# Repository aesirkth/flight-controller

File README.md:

# Flight Controller <!-- omit in toc -->

This is the embedded software on the Flight Controller for the project Mjollnir. The Flight Controller is on-board the rocket. The Flight Controller communicates with the ground through a radio link during all phases of the flight

The mission objectives for the Mjollnir project relevant to the electronics are the following:

**Primary objectives**

- **E.PO.1** Monitor the rocket while it is on the launchpad and give a “Go”/”No go” signal
- **E.PO.2** Control the rocket while it is on the launchpad
- **E.PO.3** Trigger the drogue parachute’s ejection after apogee
- **E.PO.4** Trigger the main parachute’s ejection before touchdown
- **E.PO.5** Support rocket recovery operations
- **E.PO.6** Record video footage from the rocket

**Secondary objectives**

- **E.SO.1** Send real-time telemetry from the rocket
- **E.SO.2** Receive & display real-time telemetry from the rocket at the Ground Station as long as the rocket is at a reasonable distance
- **E.SO.3** Send real-time video from the rocket
- **E.SO.4** Receive & display real-time video from the rocket at the Ground Station as long as the rocket is at a reasonable distance
- **E.SO.5** Acquire flight data with more sensors than those deemed “mission-critical”
- **E.SO.6** Store all flight data on-board the rocket for further analysis

All of them apply to some extent to the Flight Controller

# Table of content <!-- omit in toc -->

- [Description](#description)
  - [Hardware](#hardware)
  - [Software](#software)
    - [Installation](#installation)
  - [Tests](#tests)
- [Data protocol](#data-protocol)
- [Folder structure](#folder-structure)

# Description

## Hardware

The Flight Controller is a single PCB with power management, sensors, radio communication, and driver for the actuators used during the flight.

It has the following features:

- Dual microcontroller (main + backup)
- Low power long range LoRa transceiver
- Telemetry output via serial link (x3)
- GNSS support via serial link (x3)
- Compatible with 10 dof breakout board with MS5611 pressure sensors and MPU9250 IMU (2x)
- Compatible with K type thermocouples (2x)
- Flash memory
- EEDs driver for parachute ejection, with ESD protection + visual and audible warning (2x)
- RGB leds to display the board status
- Serial link to FPV transmitter
- CAN Bus

A more detailed description of the hardware is given in [doc/hardware_description.md](doc/hardware_description.md)

## Software

This repository uses [PlatformIO](https://platformio.org/) as the development tool for the two microcontrollers on the Flight Controller.

### Installation

1. Install [PlatformIO Core](https://docs.platformio.org/en/latest/core/index.html) or [PlatformIO IDE](https://platformio.org/install/ide) on your computer
2. Clone this repository
3. [Linux] install [udev](https://docs.platformio.org/en/latest/faq.html?highlight=99#platformio-udev-rules) rules

## Tests

See [test/](test/)

# Data protocol

The protocol to communicate between the Ground Station and the Rocket is detailed in [doc/data_protocol](doc/data_protocol.md)

# Folder structure

```
.
├── doc/
│   ├── img/
│   ├── diagrams/
│   ├── sources
│   |   └── flight_controller_v1.0.pdf
│   ├── data_protocol.md
│   └── hardware_description.md
├── include/
│   ├── hardware_definition_nano.h
│   └── hardware_definition_teensy.h
├── src/                                    // Code folder
│   └── test_companion_teensy.cpp           // Use with hardware_test_teensy
├── test/                                   // Unit tests
│   ├── hardware_test_nano/
│   ├── hardware_test_teensy/
│   └── README.md                           // Documentation for the tests
├── env_nano.ini                            // Extra platformIO config
├── env_teensy.ini                          // Extra platformIO config
├── LICENSE
├── platformio.ini                          // PlatformIO config
└── README.md                               // This file
```

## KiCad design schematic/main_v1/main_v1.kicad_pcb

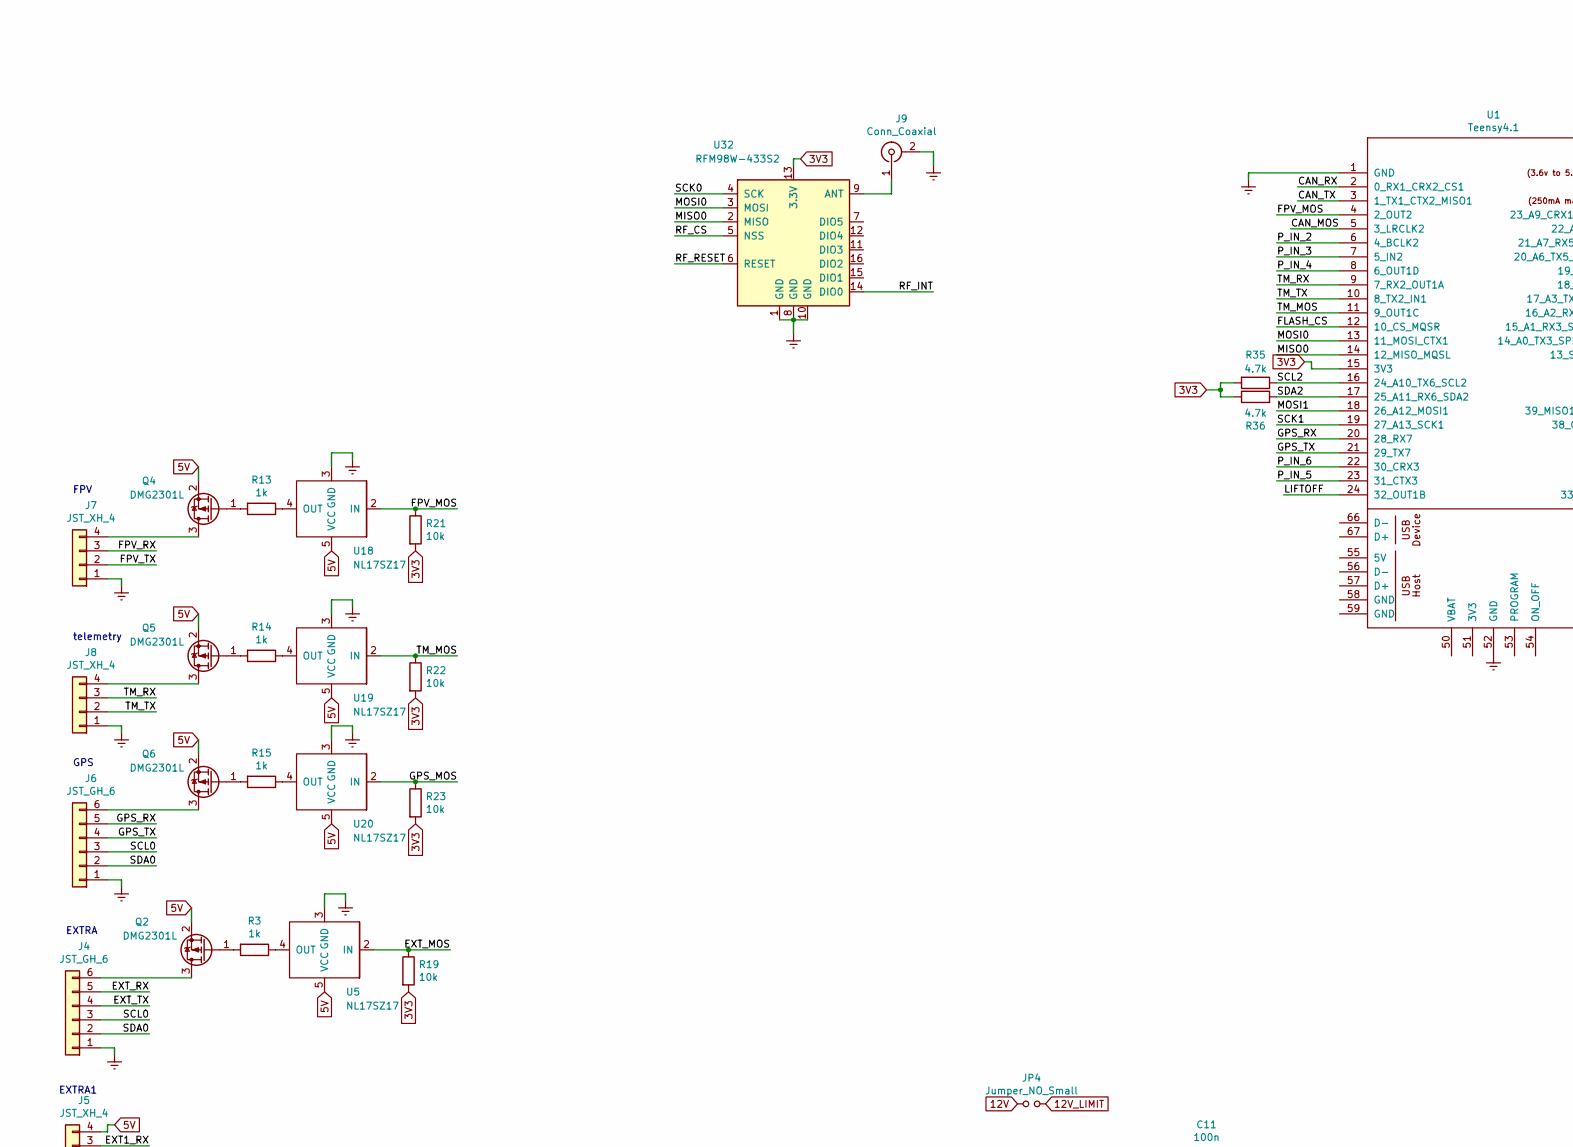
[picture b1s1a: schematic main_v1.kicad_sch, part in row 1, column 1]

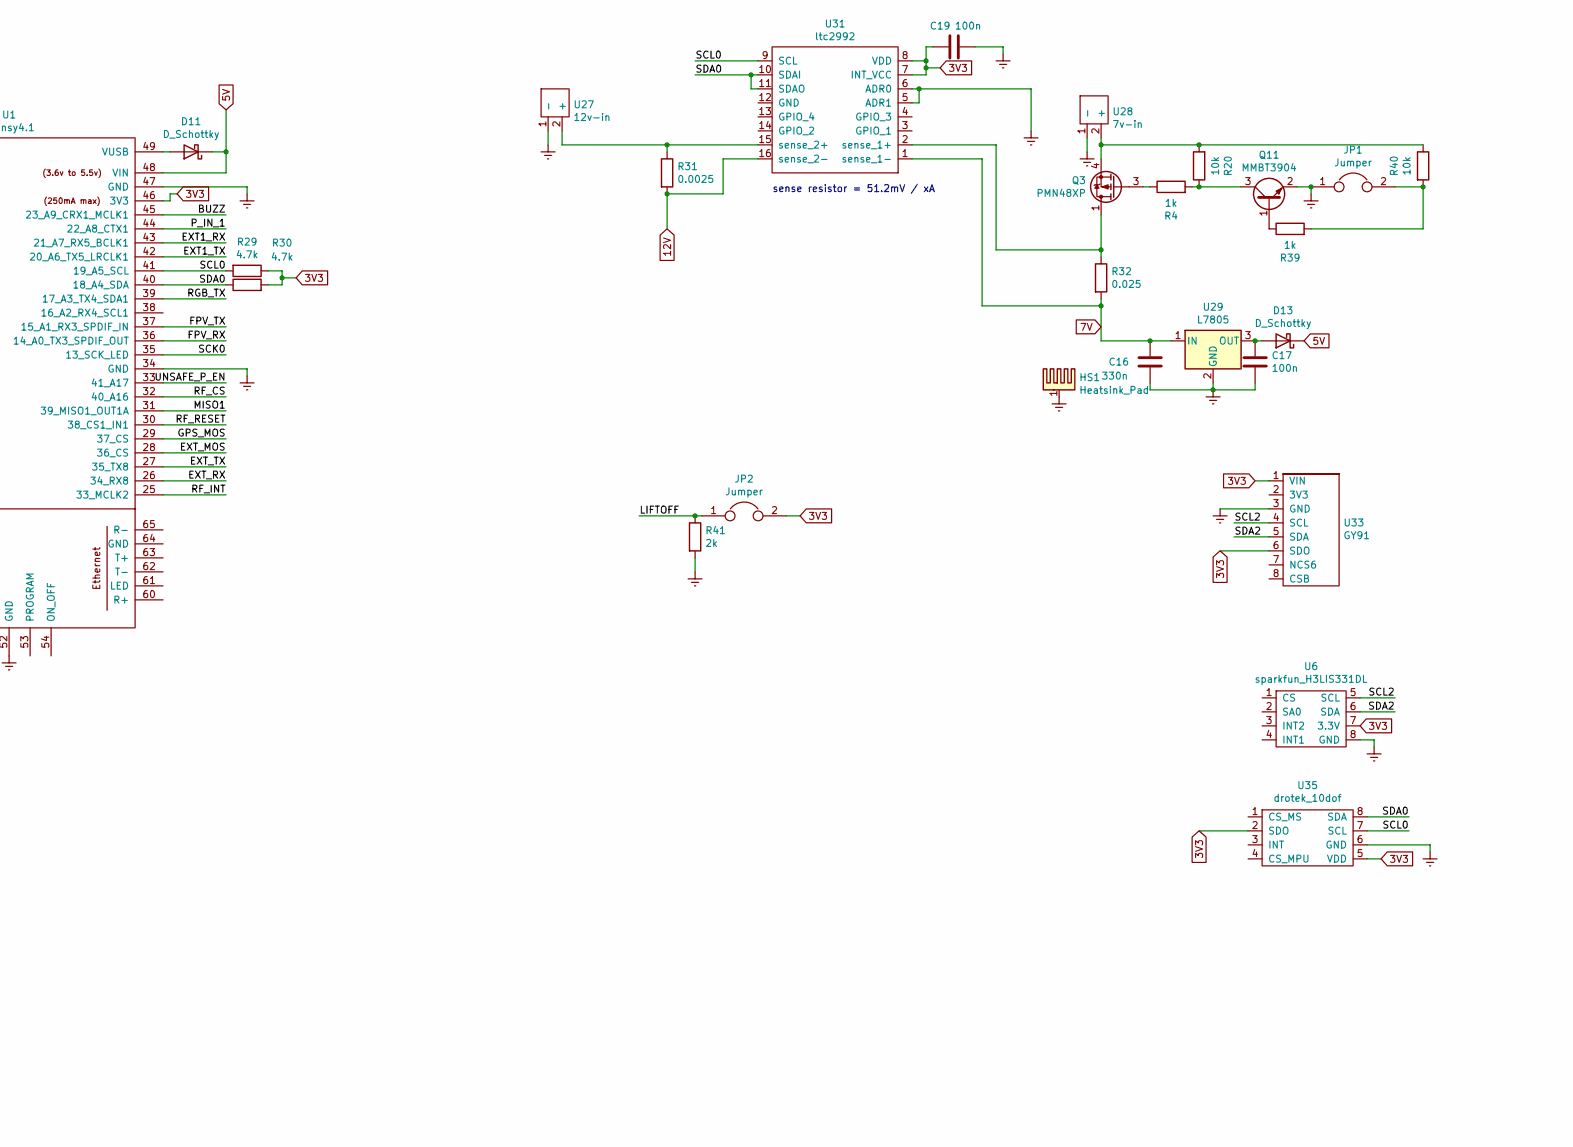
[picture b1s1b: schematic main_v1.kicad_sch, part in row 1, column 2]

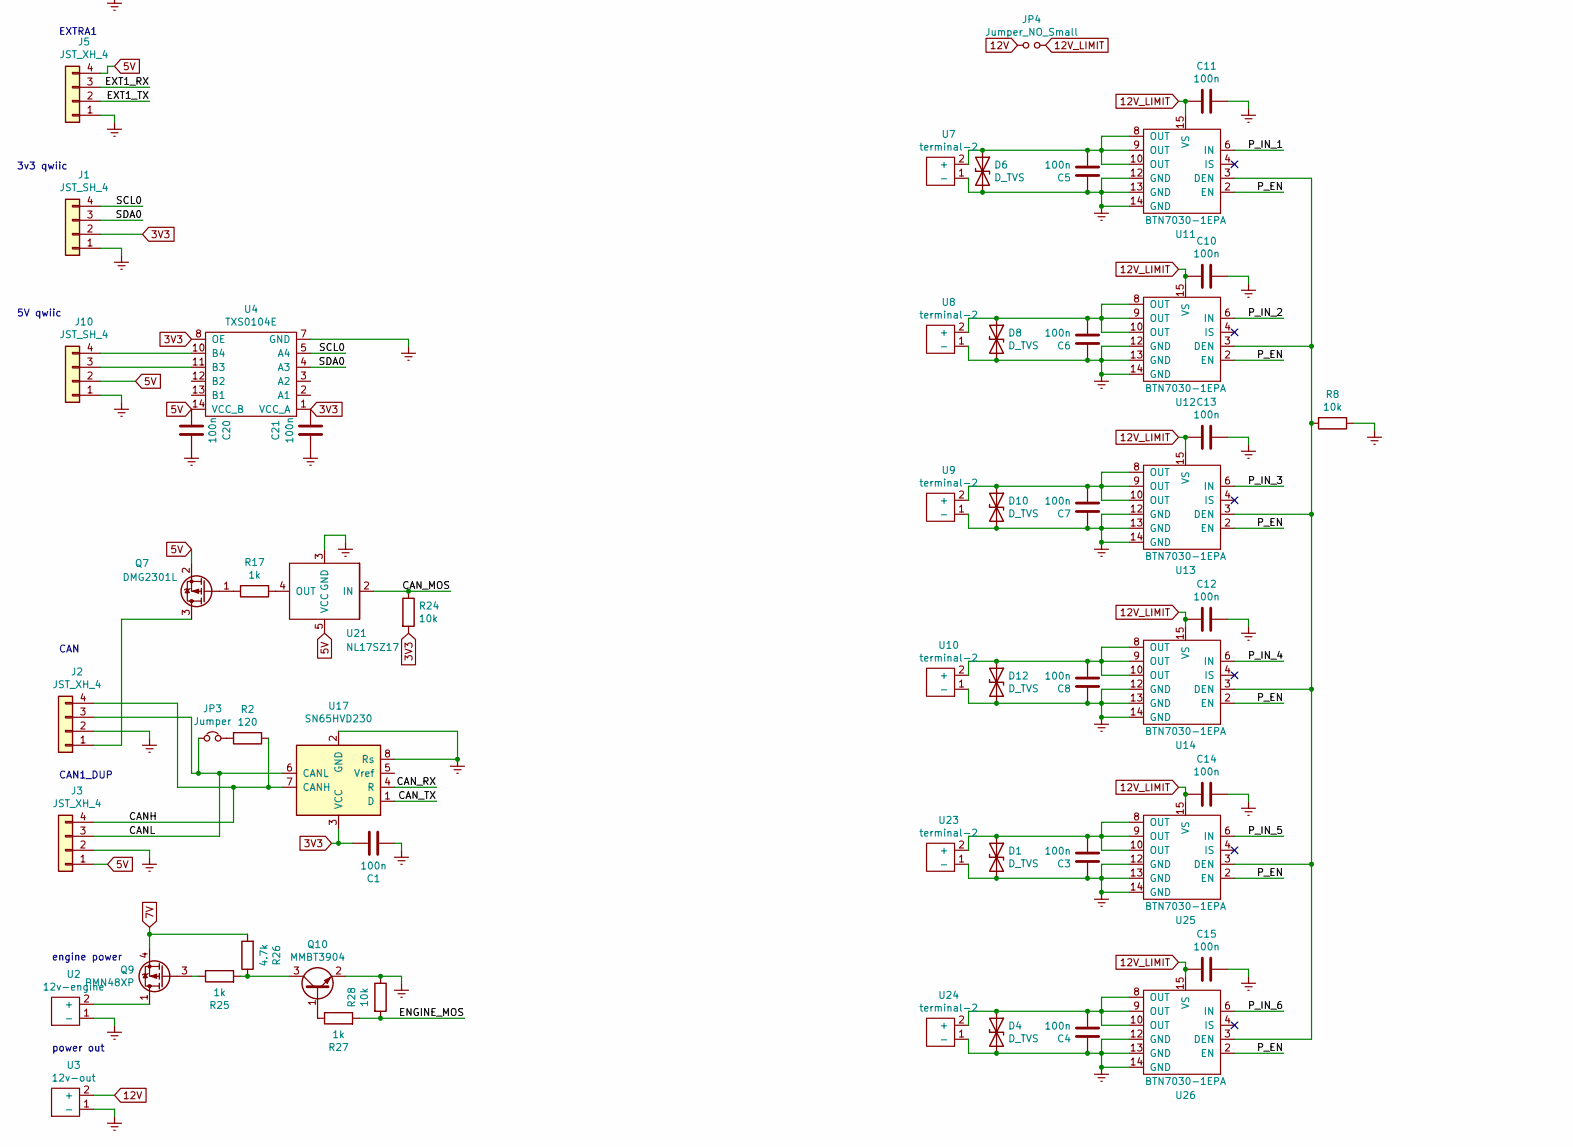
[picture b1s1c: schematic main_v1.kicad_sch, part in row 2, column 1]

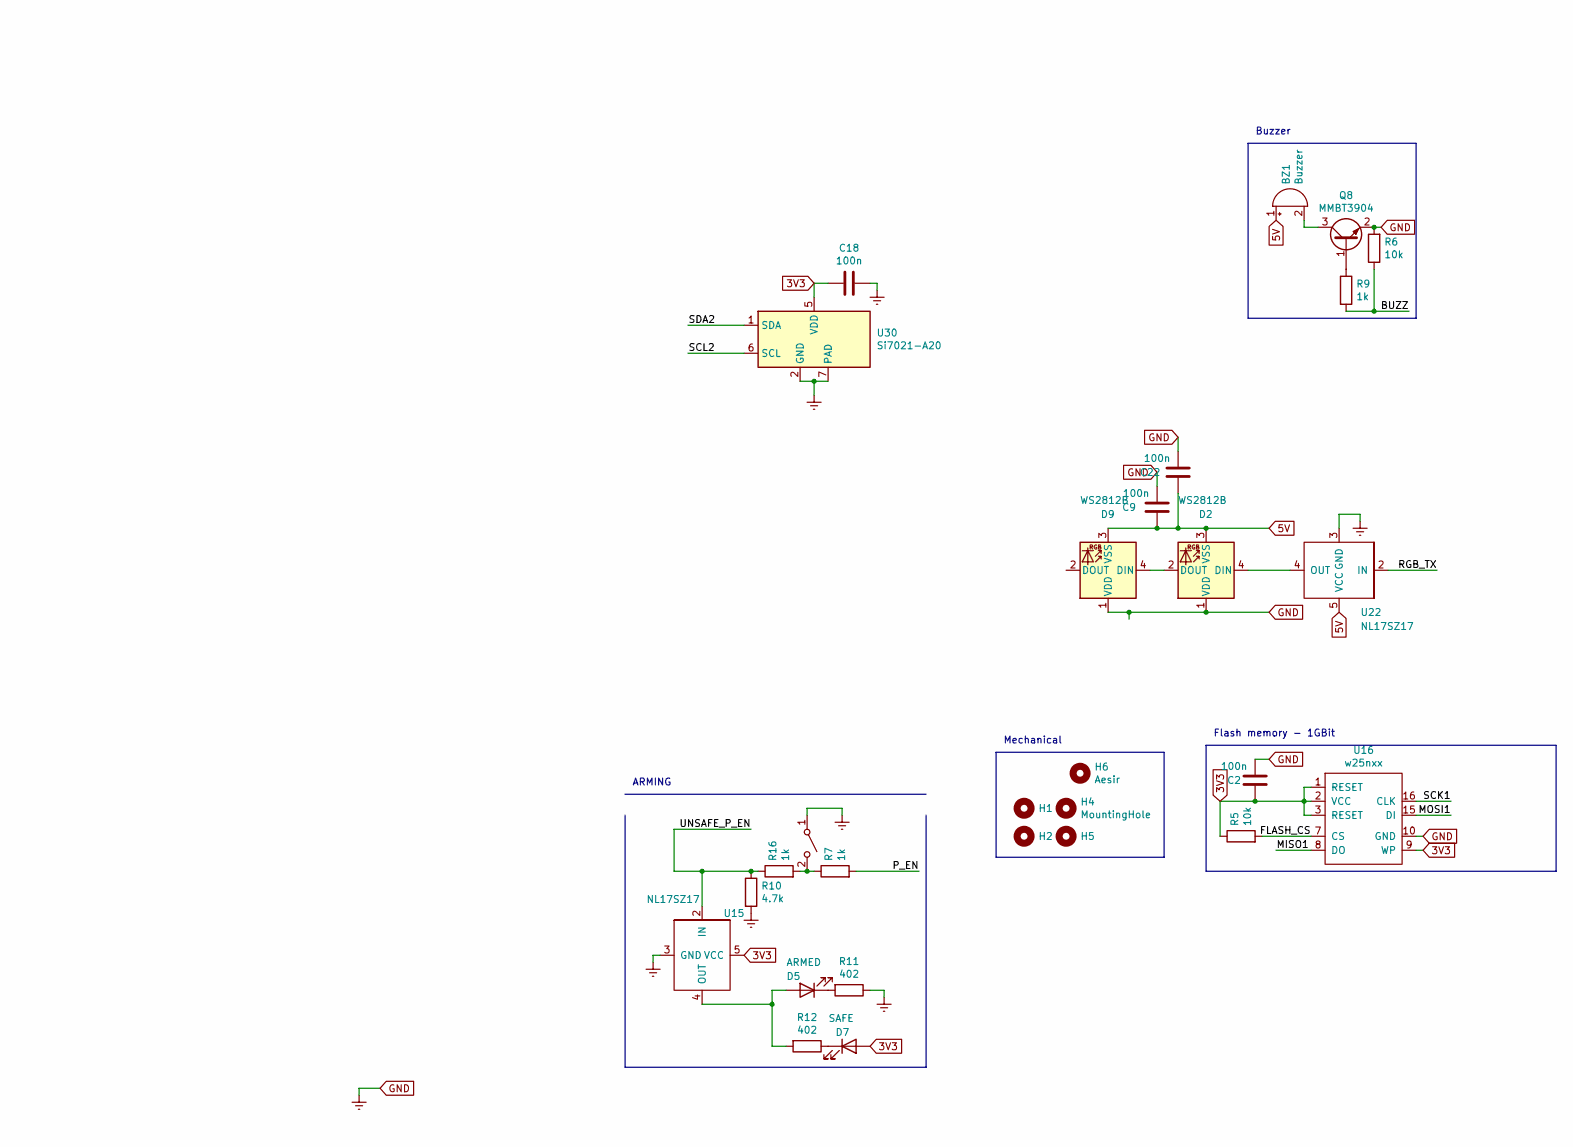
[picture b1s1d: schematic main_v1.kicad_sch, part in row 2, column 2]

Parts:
BZ1: Buzzer; CX-0905C; mouser 490-CX-0905C
C1, C2, C3, C4, C5, C6, C7, C8, C9, C10, C11, C12, C13, C14, C15, C17, C18, C19, C20, C21, C22: 100n; C_0805_2012Metric_Pad1.18x1.45mm_HandSolder; mouser 710-885012207072
C16: 330n; C_0805_2012Metric_Pad1.18x1.45mm_HandSolder; mouser 80-C0805C334K3N
D1, D4, D6, D8, D10, D12: D_TVS; D_0805_2012Metric_Pad1.15x1.40mm_HandSolder; mouser 621-SD15C-7
D2, D9: WS2812B; ws2812-through-hole-5mm
D5: ARMED; LED_0805_2012Metric_Pad1.15x1.40mm_HandSolder; mouser 710-150060AS75000
D7: SAFE; LED_0805_2012Metric_Pad1.15x1.40mm_HandSolder; mouser 710-150060YS75000
D11, D13: D_Schottky; D_SOD-323_HandSoldering; mouser 726-BAT60AE6327XT
H1, H2, H4, H5: MountingHole; MountingHole_3.2mm_M3_ISO14580
H6: Aesir; aesir
HS1: Heatsink_Pad; d2pak_heatsink; mouser 588-DV-T263-201E-TR
J1, J10: JST_SH_4; JST_SH_SM04B-SRSS-TB_1x04-1MP_P1.00mm_Horizontal; mouser 485-4208
J2, J3, J5, J7, J8: JST_XH_4; JST_XH_B4B-XH-A_1x04_P2.50mm_Vertical
J4, J6: JST_GH_6; JST_GH_BM06B-GHS-TBT_1x06-1MP_P1.25mm_Vertical
J9: Conn_Coaxial; SMA_Amphenol_132289_EdgeMount; mouser 712-CONSMA020.062-G
JP1, JP2: Jumper; JST_XH_B2B-XH-A_1x02_P2.50mm_Vertical
JP3: Jumper; PinHeader_1x02_P2.54mm_Vertical
JP4: Jumper_NO_Small; R_1812_4532Metric_Pad1.30x3.40mm_HandSolder_no_silk
Q2, Q4, Q5, Q6, Q7: DMG2301L; SOT-23; mouser 621-DMG2301L-7
Q3, Q9: PMN48XP; TSOP-6_1.65x3.05mm_P0.95mm; mouser 771-PMN48XP,125
Q8, Q10, Q11: MMBT3904; SOT-23; mouser 241-MMBT3904R200001
R2: 120; R_0805_2012Metric_Pad1.20x1.40mm_HandSolder; mouser 652-CR0805FX-1200ELF
R3, R4, R7, R9, R13, R14, R15, R16, R17, R25, R27, R39: 1k; R_0805_2012Metric_Pad1.20x1.40mm_HandSolder; mouser 667-ERJ-6ENF1001V
R5, R6, R8, R19, R20, R21, R22, R23, R24, R28, R40: 10k; R_0805_2012Metric_Pad1.20x1.40mm_HandSolder; mouser 71-CRCW080510K0FKEAC
R10, R26, R29, R30, R35, R36: 4.7k; R_0805_2012Metric_Pad1.20x1.40mm_HandSolder; mouser 652-CR0805FX-4701ELF
R11, R12: 402; R_0805_2012Metric_Pad1.20x1.40mm_HandSolder; mouser 603-RT0805FRE07402RL
R31: 0.0025; R_2512_6332Metric_Pad1.40x3.35mm_HandSolder; mouser 756-ULR1-R0025FT2
R32: 0.025; R_2512_6332Metric_Pad1.40x3.35mm_HandSolder; mouser WSL2512R0250FEB
R41: 2k; R_0805_2012Metric_Pad1.20x1.40mm_HandSolder; mouser 71-CRCW08052K00FKEAC
SW1: SW_DPST_x2; PinHeader_1x02_P2.54mm_Vertical
U1: Teensy4.1; Teensy41
U2: 12v-engine; AMASS_XT30U-F_1x02_P5.0mm_Vertical
U3: 12v-out; AMASS_XT30U-F_1x02_P5.0mm_Vertical
U4: TXS0104E; TSSOP-14_4.4x5mm_P0.65mm; mouser 771-LSF0204PW-Q100J
U5, U15, U18, U19, U20, U21, U22: NL17SZ17; SC-74-a; mouser 863-NL17SZ17DBVT1G
U6: sparkfun_H3LIS331DL; mouser 474-SEN-14480
U7, U8, U9, U10, U23, U24: terminal-2; terminal-small
U11, U12, U13, U14, U25, U26: BTN7030-1EPA; Infineon_PG-TSDSO-14-22-bottom; mouser 726-BTN70301EPAXUMA1
U16: w25nxx; SOIC-16W_7.5x10.3mm_P1.27mm; mouser 454-W25N01GVSFIG
U17: SN65HVD230; SOIC-8_3.9x4.9mm_P1.27mm; mouser 595-SN65HVD231QDRQ1
U27: 12v-in; AMASS_XT60-M_1x02_P7.20mm_Vertical
U28: 7v-in; AMASS_XT30U-M_1x02_P5.0mm_Vertical
U29: L7805; TO-263-2; mouser 511-L7805ABD2T-TR
U30: Si7021-A20; DFN-6-1EP_3x3mm_P1mm_EP1.5x2.4mm; mouser 634-SI7021-A20-IM
U31: ltc2992; MSOP-16_3x4mm_P0.5mm; mouser 584-LTC2992IMSPBF
U32: RFM98W-433S2; HOPERF_RFM9XW_SMD; mouser :(
U33: GY91
U35: drotek_10dof

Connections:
3V3: C1.2, C2.1, C18.2, C19.2, C21.1, D7.2 (A), J1.2, JP2.2, R5.1, R19.2, R21.2, R22.2, R23.2, R24.2, R29.1, R30.2, R35.2, R36.1, U1.15 (3V3), U1.46 (3V3), U4.1 (VCC_A), U4.8 (OE), U6.7 (3.3V), U15.5 (VCC), U16.1 (RESET), U16.2 (VCC), U16.3 (RESET), U16.9 (WP), U17.3 (VCC), U30.5 (VDD), U31.7 (INT_VCC), U31.8 (VDD), U32.13 (3.3V), U33.1 (VIN), U33.6 (SDO), U35.2 (SDO), U35.5 (VDD)
5V: BZ1.1 (-), C9.1, C20.2, C22.1, D2.3 (VSS), D9.3 (VSS), D11.1 (K), D13.1 (K), J3.1, J5.4, J10.2, Q2.2 (S), Q4.2 (S), Q5.2 (S), Q6.2 (S), Q7.2 (S), U1.48 (VIN), U4.14 (VCC_B), U5.5 (VCC), U18.5 (VCC), U19.5 (VCC), U20.5 (VCC), U21.5 (VCC), U22.5 (VCC)
7V: C16.1, Q9.4 (S), R26.2, R32.2, U29.1 (IN), U31.1 (sense_1-)
12V: JP4.1, R31.2, U3.2 (+), U31.16 (sense_2-)
12V_LIMIT: C10.2, C11.2, C12.2, C13.2, C14.2, C15.2, JP4.2, U11.15 (VS), U12.15 (VS), U13.15 (VS), U14.15 (VS), U25.15 (VS), U26.15 (VS)
/BUZZ: R6.1, R9.2, U1.45 (23_A9_CRX1_MCLK1)
/CAN_MOS: R24.1, U1.5 (3_LRCLK2), U21.2 (IN)
/CAN_RX: U1.2 (0_RX1_CRX2_CS1), U17.4 (R)
/CAN_TX: U1.3 (1_TX1_CTX2_MISO1), U17.1 (D)
/ENGINE_MOS: R27.2, R28.2
/EXT1_RX: J5.3, U1.43 (21_A7_RX5_BCLK1)
/EXT1_TX: J5.2, U1.42 (20_A6_TX5_LRCLK1)
/EXT_MOS: R19.1, U1.28 (36_CS), U5.2 (IN)
/EXT_RX: J4.5, U1.26 (34_RX8)
/EXT_TX: J4.4, U1.27 (35_TX8)
/FLASH_CS: R5.2, U1.12 (10_CS_MQSR), U16.7 (CS)
/FPV_MOS: R21.1, U1.4 (2_OUT2), U18.2 (IN)
/FPV_RX: J7.3, U1.36 (14_A0_TX3_SPDIF_OUT)
/FPV_TX: J7.2, U1.37 (15_A1_RX3_SPDIF_IN)
/GPS_MOS: R23.1, U1.29 (37_CS), U20.2 (IN)
/GPS_RX: J6.5, U1.20 (28_RX7)
/GPS_TX: J6.4, U1.21 (29_TX7)
/LIFTOFF: JP2.1, R41.1, U1.24 (32_OUT1B)
/MISO0: U1.14 (12_MISO_MQSL), U32.2 (MISO)
/MISO1: U1.31 (39_MISO1_OUT1A), U16.8 (DO)
/MOSI0: U1.13 (11_MOSI_CTX1), U32.3 (MOSI)
/MOSI1: U1.18 (26_A12_MOSI1), U16.15 (DI)
/P_EN: R7.2, U11.2 (EN), U12.2 (EN), U13.2 (EN), U14.2 (EN), U25.2 (EN), U26.2 (EN)
/P_IN_1: U1.44 (22_A8_CTX1), U11.6 (IN)
/P_IN_2: U1.6 (4_BCLK2), U12.6 (IN)
/P_IN_3: U1.7 (5_IN2), U13.6 (IN)
/P_IN_4: U1.8 (6_OUT1D), U14.6 (IN)
/P_IN_5: U1.23 (31_CTX3), U25.6 (IN)
/P_IN_6: U1.22 (30_CRX3), U26.6 (IN)
/RF_CS: U1.32 (40_A16), U32.5 (NSS)
/RF_INT: U1.25 (33_MCLK2), U32.14 (DIO0)
/RF_RESET: U1.30 (38_CS1_IN1), U32.6 (RESET)
/RGB_TX: U1.39 (17_A3_TX4_SDA1), U22.2 (IN)
/SCK0: U1.35 (13_SCK_LED), U32.4 (SCK)
/SCK1: U1.19 (27_A13_SCK1), U16.16 (CLK)
/SCL0: J1.4, J4.3, J6.3, R29.2, U1.41 (19_A5_SCL), U4.5 (A4), U31.9 (SCL), U35.7 (SCL)
/SCL2: R35.1, U1.16 (24_A10_TX6_SCL2), U6.5 (SCL), U30.6 (SCL), U33.4 (SCL)
/SDA0: J1.3, J4.2, J6.2, R30.1, U1.40 (18_A4_SDA), U4.4 (A3), U31.10 (SDAI), U31.11 (SDAO), U35.8 (SDA)
/SDA2: R36.2, U1.17 (25_A11_RX6_SDA2), U6.6 (SDA), U30.1 (SDA), U33.5 (SDA)
/TM_MOS: R22.1, U1.11 (9_OUT1C), U19.2 (IN)
/TM_RX: J8.3, U1.9 (7_RX2_OUT1A)
/TM_TX: J8.2, U1.10 (8_TX2_IN1)
/UNSAFE_P_EN: R10.1, R16.1, U1.33 (41_A17), U15.2 (IN)
GND: C1.1, C2.2, C3.1, C4.1, C5.1, C6.1, C7.1, C8.1, C9.2, C10.1, C11.1, C12.1, C13.1, C14.1, C15.1, C16.2, C17.2, C18.1, C19.1, C20.1, C21.2, C22.2, D1.2 (A2), D2.1 (VDD), D4.2 (A2), D6.2 (A2), D8.2 (A2), D9.1 (VDD), D10.2 (A2), D12.2 (A2), HS1.1, J1.1, J2.2, J3.2, J4.1, J5.1, J6.1, J7.1, J8.1, J9.2 (Ext), J10.1, JP1.1, Q8.2 (E), Q10.2 (E), Q11.2 (E), R6.2, R8.1, R10.2, R11.1, R28.1, R41.2, SW1.1 (A), U1.1 (GND), U1.34 (GND), U1.47 (GND), U1.52 (GND), U2.1 (-), U3.1 (-), U4.7 (GND), U5.3 (GND), U6.8 (GND), U7.1 (-), U8.1 (-), U9.1 (-), U10.1 (-), U11.12 (GND), U11.13 (GND), U11.14 (GND), U12.12 (GND), U12.13 (GND), U12.14 (GND), U13.12 (GND), U13.13 (GND), U13.14 (GND), U14.12 (GND), U14.13 (GND), U14.14 (GND), U15.3 (GND), U16.10 (GND), U17.2 (GND), U17.8 (Rs), U18.3 (GND), U19.3 (GND), U20.3 (GND), U21.3 (GND), U22.3 (GND), U23.1 (-), U24.1 (-), U25.12 (GND), U25.13 (GND), U25.14 (GND), U26.12 (GND), U26.13 (GND), U26.14 (GND), U27.1 (-), U28.1 (-), U29.2 (GND), U30.2 (GND), U30.7 (PAD), U31.5 (ADR1), U31.6 (ADR0), U32.1 (GND), U32.8 (GND), U32.10 (GND), U33.3 (GND), U35.6 (GND)
unnamed: BZ1.2 (+), Q8.3 (C)
unnamed: C3.2, D1.1 (A1), U23.2 (+), U25.8 (OUT), U25.9 (OUT), U25.10 (OUT)
unnamed: C4.2, D4.1 (A1), U24.2 (+), U26.8 (OUT), U26.9 (OUT), U26.10 (OUT)
unnamed: C5.2, D6.1 (A1), U7.2 (+), U11.8 (OUT), U11.9 (OUT), U11.10 (OUT)
unnamed: C6.2, D8.1 (A1), U8.2 (+), U12.8 (OUT), U12.9 (OUT), U12.10 (OUT)
unnamed: C7.2, D10.1 (A1), U9.2 (+), U13.8 (OUT), U13.9 (OUT), U13.10 (OUT)
unnamed: C8.2, D12.1 (A1), U10.2 (+), U14.8 (OUT), U14.9 (OUT), U14.10 (OUT)
unnamed: C17.1, D13.2 (A), U29.3 (OUT)
unnamed: D2.2 (DOUT), D9.4 (DIN)
unnamed: D2.4 (DIN), U22.4 (OUT)
unnamed: D5.1 (K), R11.2
unnamed: D5.2 (A), R12.2, U15.4 (OUT)
unnamed: D7.1 (K), R12.1
unnamed: D11.2 (A), U1.49 (VUSB)
unnamed: J2.1, Q7.3 (D)
unnamed: J2.3, J3.3, JP3.1, U17.6 (CANL)
unnamed: J2.4, J3.4, R2.1, U17.7 (CANH)
unnamed: J4.6, Q2.3 (D)
unnamed: J6.6, Q6.3 (D)
unnamed: J7.4, Q4.3 (D)
unnamed: J8.4, Q5.3 (D)
unnamed: J9.1 (In), U32.9 (ANT)
unnamed: J10.3, U4.11 (B3)
unnamed: J10.4, U4.10 (B4)
unnamed: JP1.2, R39.2, R40.2
unnamed: JP3.2, R2.2
unnamed: Q2.1 (G), R3.2
unnamed: Q3.1 (D), Q3.2 (D), Q3.5 (D), Q3.6 (D), R32.1, U31.2 (sense_1+)
unnamed: Q3.3 (G), R4.1
unnamed: Q3.4 (S), R20.2, R40.1, U28.2 (+)
unnamed: Q4.1 (G), R13.2
unnamed: Q5.1 (G), R14.2
unnamed: Q6.1 (G), R15.2
unnamed: Q7.1 (G), R17.2
unnamed: Q8.1 (B), R9.1
unnamed: Q9.1 (D), Q9.2 (D), Q9.5 (D), Q9.6 (D), U2.2 (+)
unnamed: Q9.3 (G), R25.1
unnamed: Q10.1 (B), R27.1
unnamed: Q10.3 (C), R25.2, R26.1
unnamed: Q11.1 (B), R39.1
unnamed: Q11.3 (C), R4.2, R20.1
unnamed: R3.1, U5.4 (OUT)
unnamed: R8.2, U11.3 (DEN), U12.3 (DEN), U13.3 (DEN), U14.3 (DEN), U25.3 (DEN), U26.3 (DEN)
unnamed: R13.1, U18.4 (OUT)
unnamed: R14.1, U19.4 (OUT)
unnamed: R15.1, U20.4 (OUT)
unnamed: R7.1, R16.2, SW1.2 (B)
unnamed: R17.1, U21.4 (OUT)
unnamed: R31.1, U27.2 (+), U31.15 (sense_2+)

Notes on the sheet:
engine power
CAN1_DUP
power out
telemetry
5V qwiic
Flash memory - 1GBit
EXTRA1
3v3 qwiic
Buzzer
ARMING
EXTRA
Mechanical
GPS
CAN
FPV
sense resistor = 51.2mV / xA

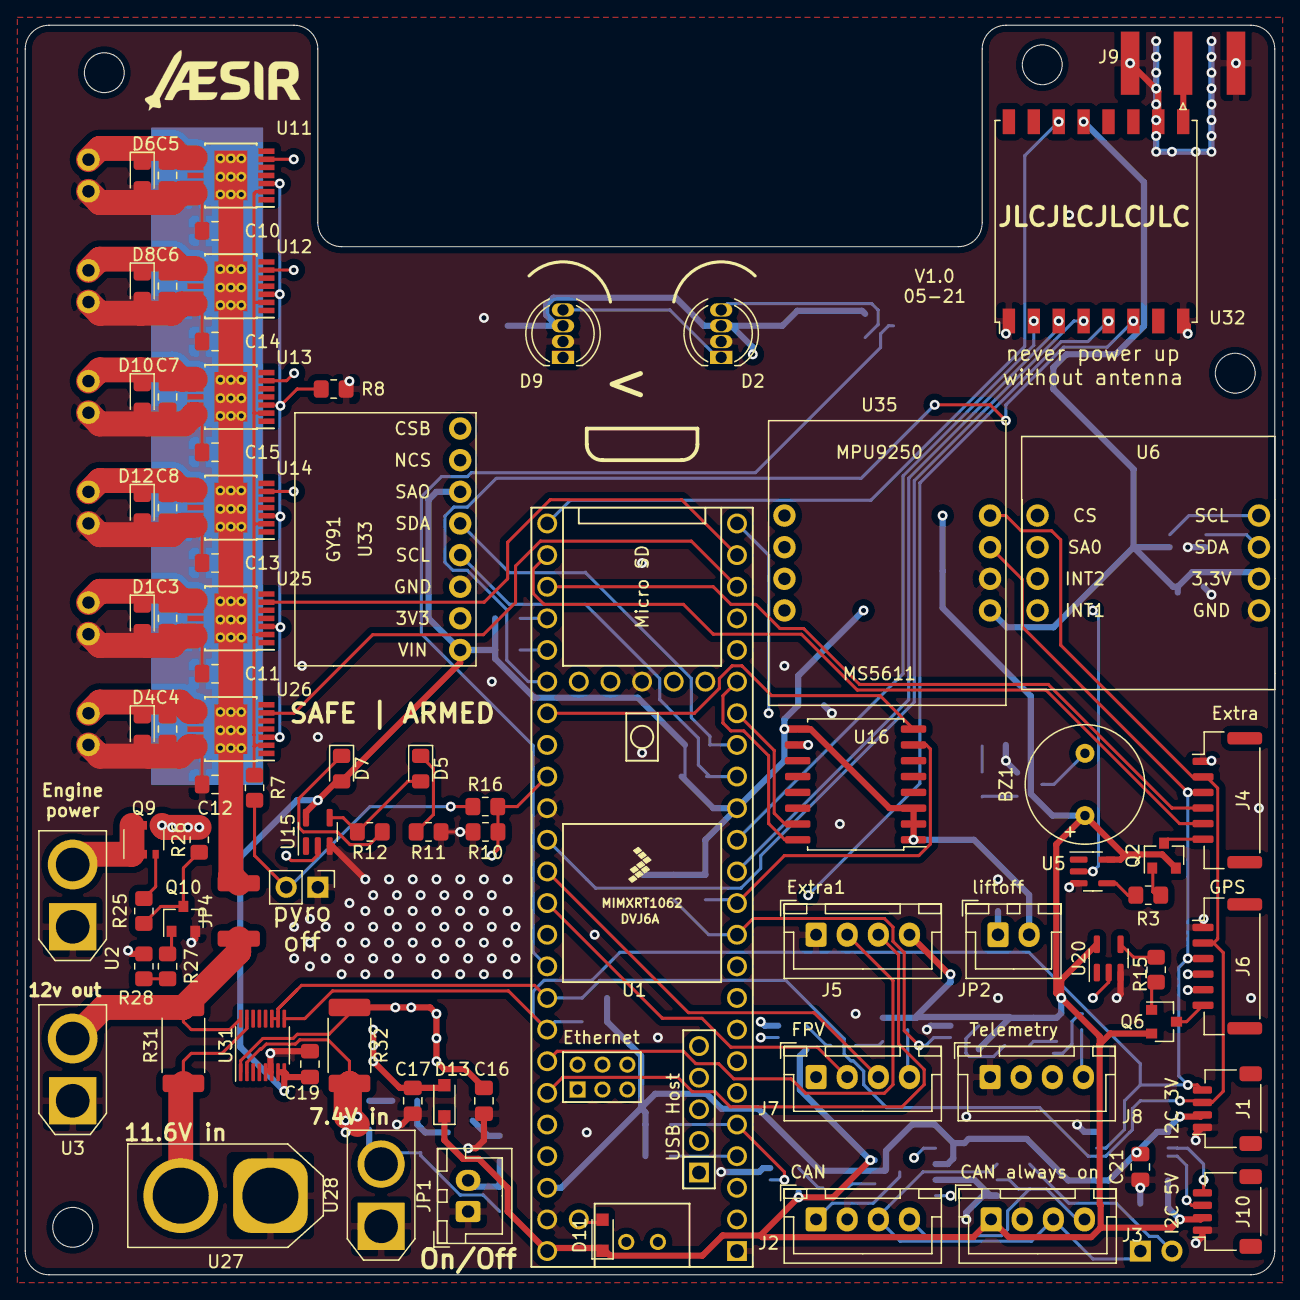
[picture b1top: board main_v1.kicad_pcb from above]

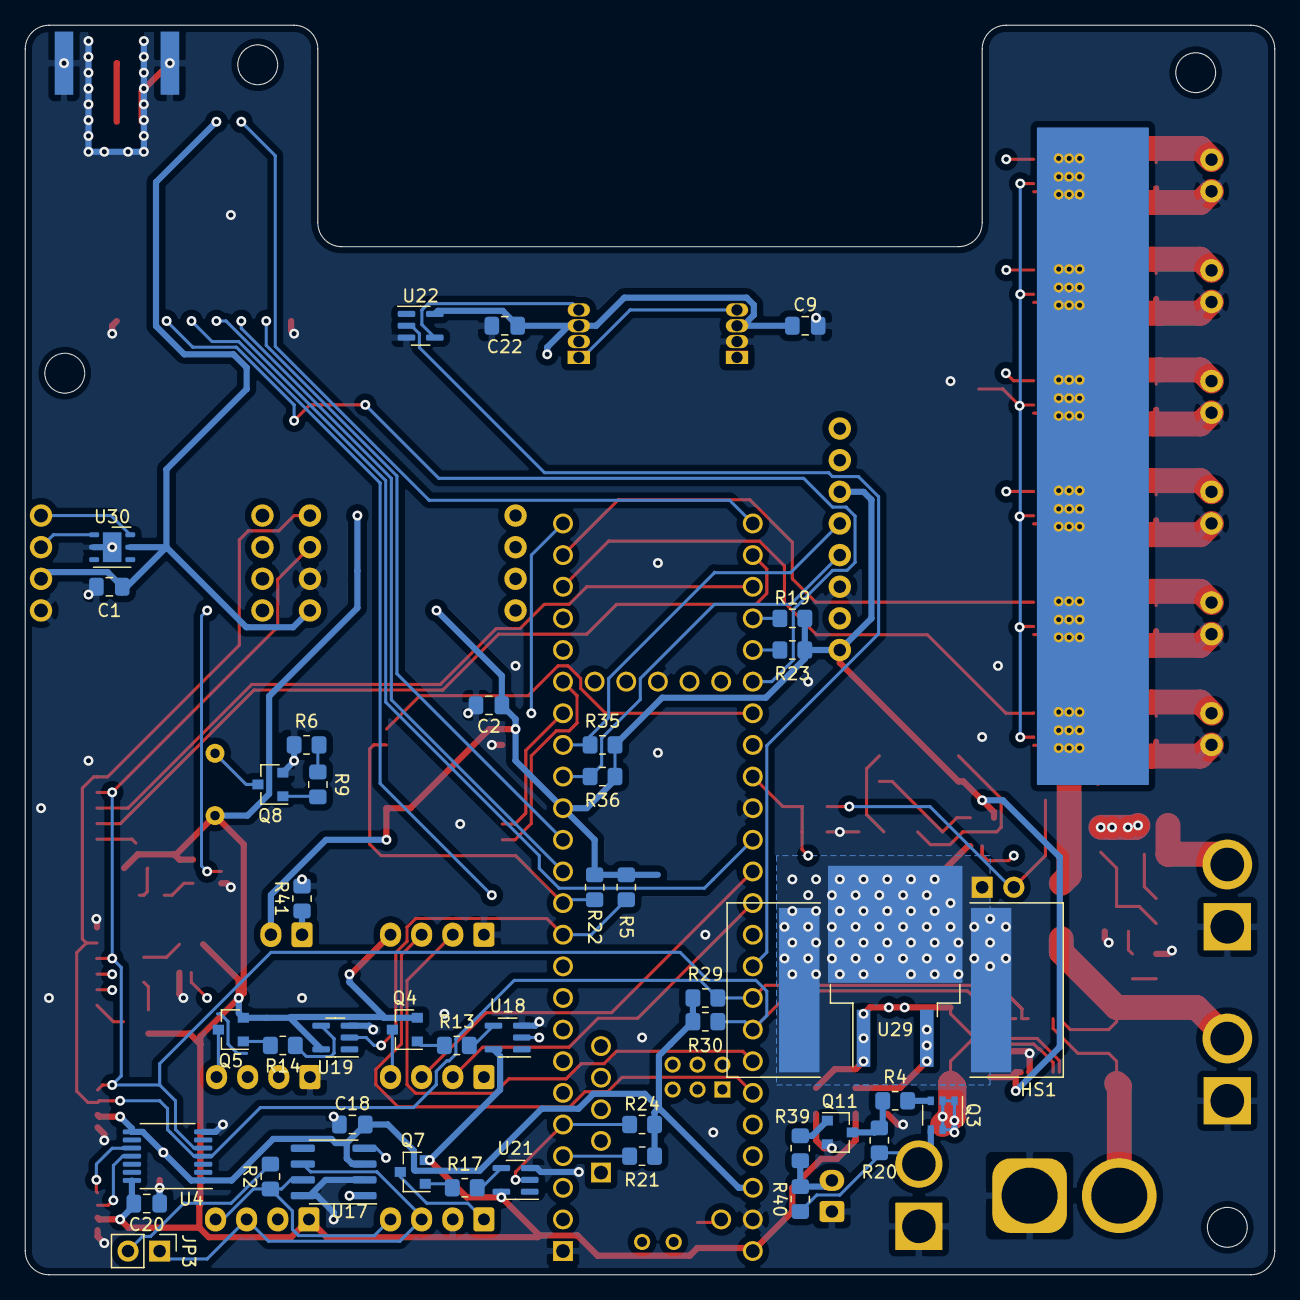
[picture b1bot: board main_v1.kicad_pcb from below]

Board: 4 copper layers, 100.3 x 100.3 mm, 135 parts (43 on the bottom side), 98 nets.

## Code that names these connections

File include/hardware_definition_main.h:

#define PIN_CAN_RX 0
#define PIN_CAN_TX 1
#define PIN_FPV_MOS 2
#define PIN_CAN_MOS 3
#define PIN_PYRO_2 4
#define PIN_PYRO_3 5
#define PIN_PYRO_4 6
#define PIN_TM_RX 7
#define PIN_TM_TX 8
#define PIN_TM_MOS 9
#define PIN_FLASH_CS 10
#define PIN_MOSI0 11
#define PIN_MISO0 12
#define PIN_SCL2 24
#define PIN_SDA2 25
#define PIN_MOSI1 26
#define PIN_SCK1 27
#define PIN_GPS_RX 28
#define PIN_GPS_TX 29
#define PIN_PYRO_6 30
#define PIN_PYRO_5 31
#define PIN_LIFTOFF 32
#define PIN_RF_INT 33
#define PIN_EXT_RX 34
#define PIN_EXT_TX 35
#define PIN_EXT_MOS 36
#define PIN_GPS_MOS 37
#define PIN_RF_RESET 38
#define PIN_MISO1 39
#define PIN_RF_CS 40
#define PIN_PYRO_EN 41
#define PIN_SCK0 13
#define PIN_FPV_RX 14
#define PIN_FPV_TX 15
#define PIN_RGB_TX 17
#define PIN_SDA0 18
#define PIN_SCL0 19
#define PIN_EXT1_TX 20
#define PIN_EXT1_RX 21
#define PIN_PYRO_1 22
#define PIN_BUZZER 23

#define TM_SERIAL Serial2
#define SPI_FLASH SPI1
#define SPI_RADIO SPI
#define GPS_SERIAL Serial7
#define EXT_SERIAL Serial8
#define FPV_SERIAL Serial3
#define RGB_SERIAL Serial4
#define EXT1_SERIAL Serial5

#define RFM_FREQUENCY 433
#define RFM_POWER 13

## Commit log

2020-08-03 doc: brief description
2020-08-03 add LICENSE
2020-08-03 doc: microcontrollers and battery inputs
2020-08-03 doc: more detailed hardware description
2020-08-03 doc: update pictures
2020-08-03 doc: center images
2020-08-05 doc: add mission objectives
2020-08-13 add TC overview
2020-08-13 add telemetry overview
2020-08-13 typo
2020-08-15 doc: update communication sequences
2020-08-15 add definition for commands to FC
2020-08-15 update ID allocation
2020-08-15 leave frame IDs non allocated for future use
2020-08-15 compress xml files
2020-08-16 Fix ID allocation for Engine Computer TM
2020-08-16 convert big table to HTML
2020-08-16 add considerations about time stamps
2020-08-16 add placeholder for time sync frame
2020-08-16 add telemetry data description
2020-08-16 add explainer for tables and xml
2020-08-16 update table formating
2020-08-16 fix details
2020-09-03 add engine computer TC
2020-09-03 add note for remaining ID values
2020-09-03 add a note about diagrams.net
2020-09-03 rewrite note on time stamps
2020-09-04 apply phrasing suggestions from @eweilow
2020-09-05 replace 'sleep mode' with 'power mode'
2020-09-05 use 'set' in commands names
2020-09-05 add hardware tests
2020-09-05 add software description
2020-09-05 add serial test
2020-09-05 add description for test file
2020-09-05 make test companion work on J1, J2, J3
2020-09-05 add comments to test file
2020-09-05 add description to test_companion_teensy
2020-09-05 doc: update test README
2020-09-05 update defines for J2 and J4
2020-09-05 add unit tests for arduino nano
2020-09-05 doc: link to the test folder
2020-09-05 doc: update folder structure
2020-09-05 doc: describe power setup
2020-09-05 doc: add board capabilities overview
2020-09-05 doc: add connectors
2020-09-05 doc: add purpose of FC v1.0
2020-09-05 doc: fix omega symbol
2020-09-05 doc: rename data_protocol file
2020-09-05 doc: describe FC chips
2020-09-05 doc: a word on parachute drivers
2020-09-05 add eagle source files
2020-10-25 Stratospheric Balloon Project dev branch
2020-10-25 Expanded data_protocol.md telemetry section
2020-11-03 GPS support and minor tweaks to data_protocol.h
2020-11-03 Corrections on GNSS time and data
2020-11-05 Ver 0.1
2020-11-28 Data protocol description updated
2020-11-28 Update README.md
    Link broken to data_protocol documentation
2020-12-16 Started working on implementation of RadioHead lib
2020-12-27 Add nmea parser
2020-12-28 Basic example of Flash Memory operation. Started implementation of dedicated library
2020-12-28 Basic read functions work. Added check for factory bad blocks identification
2020-12-28 Added support for reading BBM LUT
2020-12-29 fix dependencies
2020-12-29 rename files
2021-01-26 Implemented library for SPI1
2021-01-27 fix examples
2021-01-30 Writing error figured out. https://stackoverflow.com/a/44551298
2021-02-05 clean up
2021-02-09 Finally working
2021-02-23 Removed unnecesary comments
2021-02-25 remove engine stuff, add time, add flash
2021-02-25 small fixes
2021-02-25 Update doc/data_protocol.md
    typo
2021-02-27 update ranges
2021-02-27 update GNSS data
2021-03-02 update gps, data protocol, telecommand
2021-03-16 add handshake
2021-03-16 replace libraries with local version, work on main loop, protocol generation
2021-03-18 implement code generation
2021-03-26 update codegen
2021-03-26 Add limits to radiohead
2021-03-26 Created environment and started implementing relay code.
2021-03-26 Started implementing relay code; not yet tested
2021-03-28 fix error checking
2021-03-28 Add Edda relaying, update codegen
2021-04-12 preliminary DMA
2021-04-13 better structure
2021-04-13 Relay working decently
2021-04-13 update DataProtocol, relay handshake
2021-04-13 update codegen and DataProtocol
2021-04-19 Update flash chip lib
2021-04-21 Testing pressure sensor
2021-05-04 Added async sensor reading
2021-05-04 small fix
2021-05-11 restructure
2021-05-26 test code for pitot tube
2021-05-26 change LoRa to RFD
2021-11-20 total chaos
2021-12-04 pre cold test
2022-01-24 everything
2022-03-20 Adding of a spool class for telemetry
2022-04-10 Minor change
2022-04-24 Correction of the data protocol (header)
2022-04-24 Correction of the checksum
2024-05-18 bajs
